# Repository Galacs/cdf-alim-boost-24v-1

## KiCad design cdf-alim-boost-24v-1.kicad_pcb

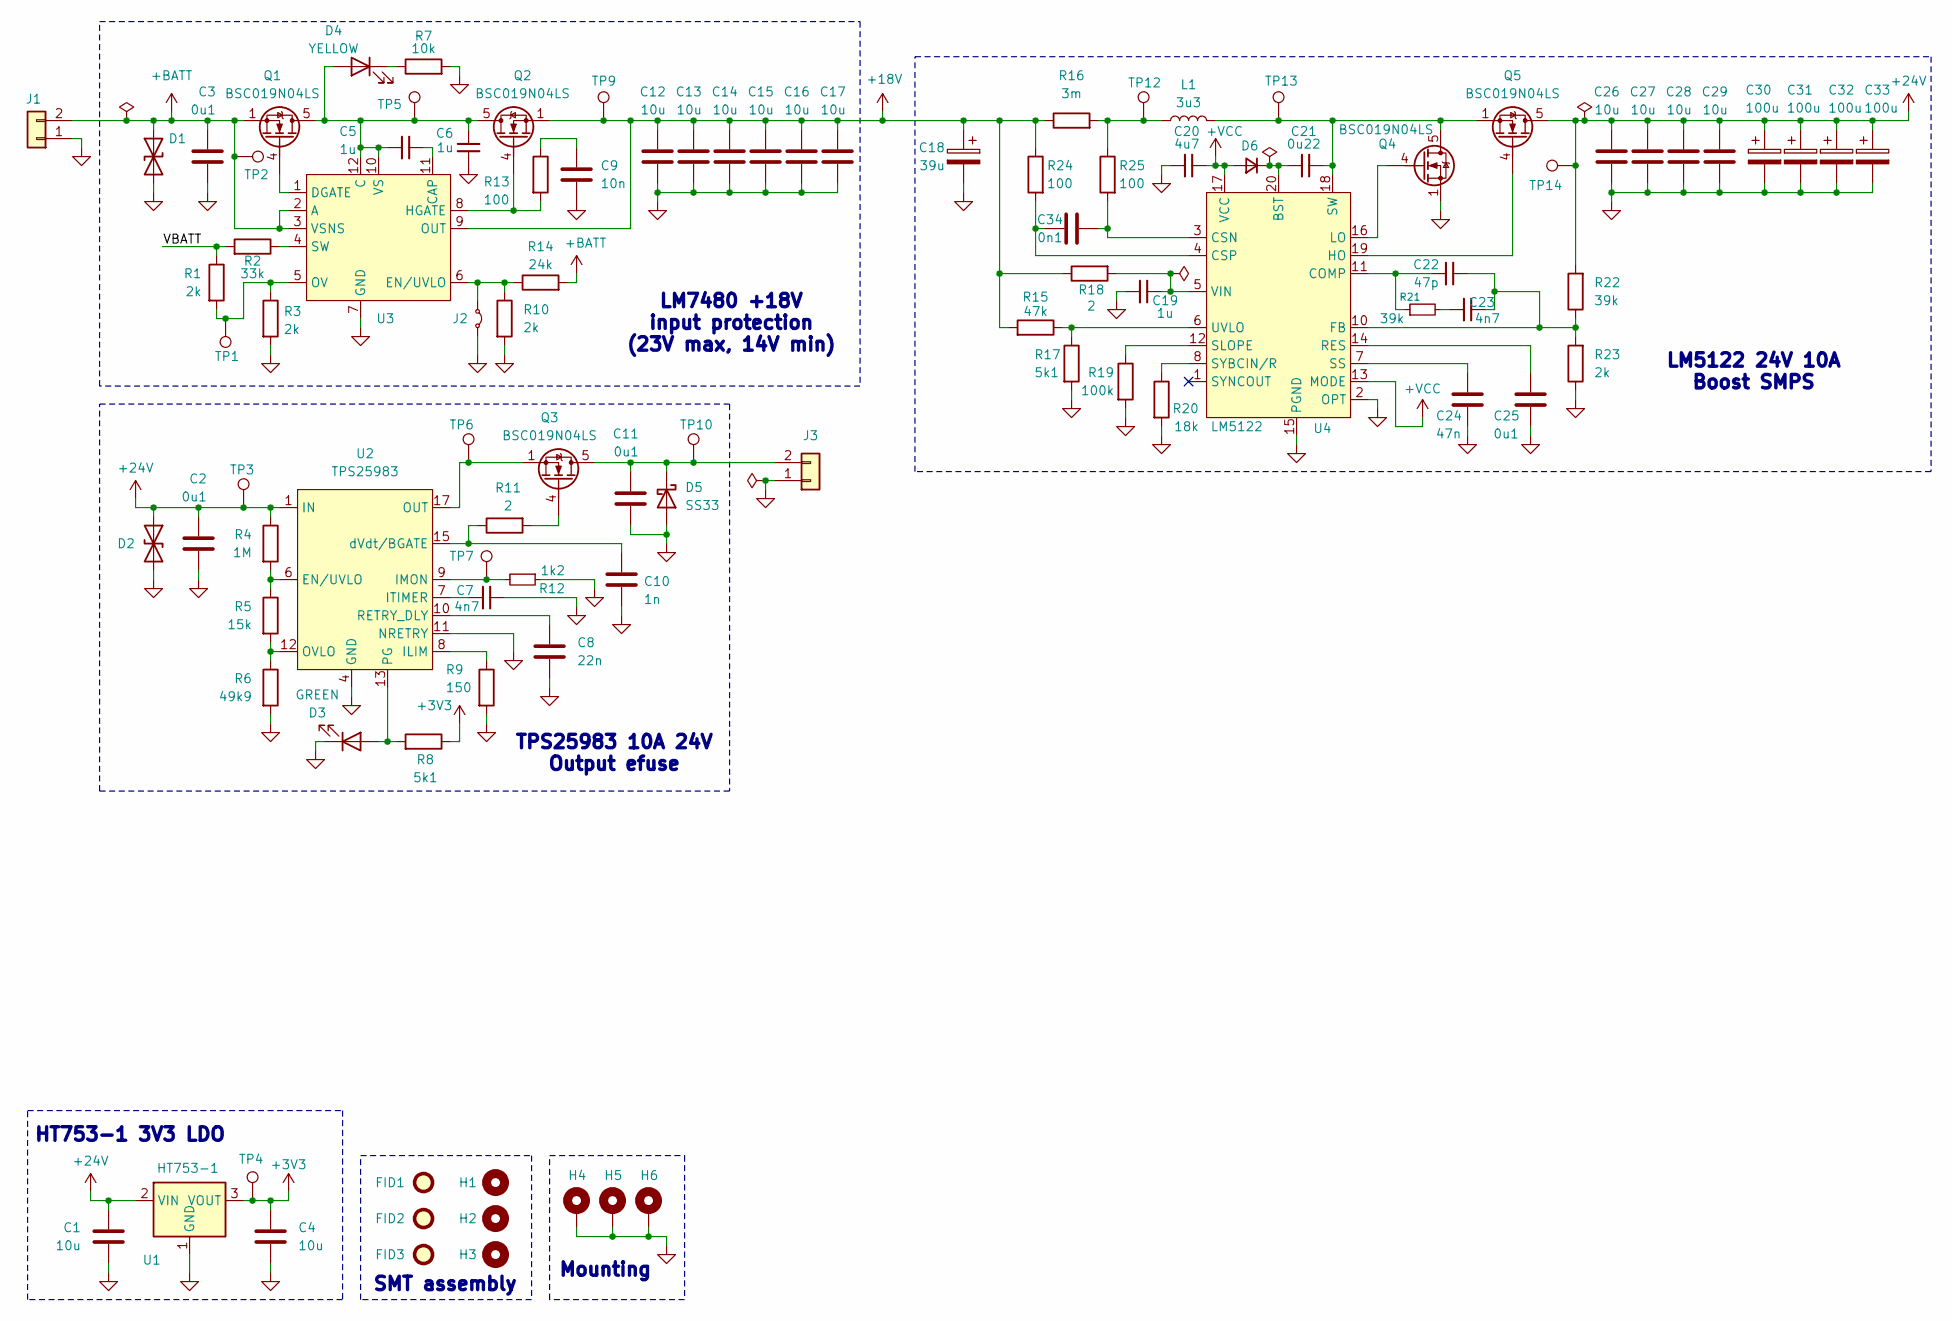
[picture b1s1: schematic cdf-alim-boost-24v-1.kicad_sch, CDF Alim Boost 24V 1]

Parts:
C1, C4: 10u; C_0805_2012Metric; Manufacturer Part Number GRM21BR61H106KE43L; JLCPCB Part # C440198
C2, C3, C11, C25: 0u1; C_0402_1005Metric; Manufacturer Part Number CL05B104KB54PNC; JLCPCB Part # C307331
C5, C6: 1u; C_0402_1005Metric; Manufacturer Part Number CL05A105KA5NQNC; JLCPCB Part # C52923
C7, C23: 4n7; C_0402_1005Metric; Manufacturer Part Number 0402B472K500NT; JLCPCB Part # C1538
C8: 22n; C_0402_1005Metric; Manufacturer Part Number 0402B223K500NT; JLCPCB Part # C1532
C9: 10n; C_0402_1005Metric; Manufacturer Part Number CL05B103KB5NNNC; JLCPCB Part # C15195
C10: 1n; C_0603_1608Metric_Pad1.08x0.95mm_HandSolder; Manufacturer Part Number CL10B102KB8NNNC; JLCPCB Part # C1588
C12, C13, C14, C15, C16, C17, C26, C27, C28, C29: 10u; C_1206_3216Metric; Manufacturer Part Number CL31A106KBHNNNE; JLCPCB Part # C13585
C18: 39u; CP_Elec_8x6.9; Manufacturer Part Number 35SVPF39M; JLCPCB Part # C189474
C19: 1u; C_0603_1608Metric_Pad1.08x0.95mm_HandSolder; Manufacturer Part Number CL10A105KB8NNNC; JLCPCB Part # C15849
C20: 4u7; C_0603_1608Metric_Pad1.08x0.95mm_HandSolder; Manufacturer Part Number CL10A475KO8NNNC; JLCPCB Part # C19666
C21: 0u22; C_0402_1005Metric; Manufacturer Part Number CL05B224KO5NNNC; JLCPCB Part # C16772
C22: 47p; C_0402_1005Metric; Manufacturer Part Number 0402CG470J500NT; JLCPCB Part # C1567
C24: 47n; R_0603_1608Metric; Manufacturer Part Number CL10B473KB8NNNC; JLCPCB Part # C1622
C30, C31, C32, C33: 100u; CP_Elec_8x10; Manufacturer Part Number RHS1V101MCN1GS; JLCPCB Part # C2162472
C34: 0n1; C_0402_1005Metric; Manufacturer Part Number 0402CG101J500NT; JLCPCB Part # C1546
D1, D2: SMAJ26CA; D_SMA; Manufacturer Part Number SMAJ26CA; JLCPCB Part # C19077544
D3: GREEN; LED_0805_2012Metric; Manufacturer Part Number KT-0805G; JLCPCB Part # C2297
D4: YELLOW; LED_0805_2012Metric; Manufacturer Part Number KT-0805Y; JLCPCB Part # C2296
D5: SS33; D_SMA; Manufacturer Part Number SS33; JLCPCB Part # C28646294
D6: D_Small; D_SMA; Manufacturer Part Number SS210; JLCPCB Part # C14996
FID1, FID2, FID3: Fiducial; Fiducial_1mm_Mask2mm
H1, H2, H3: MountingHole; ToolingHole_1.152mm
H4, H5, H6: MountingHole_Pad; MountingHole_3.2mm_M3_Pad_Via
J1: Conn_01x02; AMASS_XT30PW-M_1x02_P2.50mm_Horizontal; Manufacturer Part Number XT30PW-M30.G.Y; JLCPCB Part # C431092
J2: Conn_01x02; JST_XH_S2B-XH-A-1_1x02_P2.50mm_Horizontal; Manufacturer Part Number S2B-XH-A-1(LF)(SN); JLCPCB Part # C163035
J3: Conn_01x02; AMASS_XT30PW-F_1x02_P2.50mm_Horizontal; Manufacturer Part Number XT30PW-F20.G.Y; JLCPCB Part # C2913282
L1: 3u3; L_Sunlord_MWSA1205S-3R3; Manufacturer Part Number MWSA1205S-3R3MT; JLCPCB Part # C408513
Q1, Q2, Q3, Q4, Q5: BSC019N04LS; TDSON-8-1; Manufacturer Part Number BSC019N04LS; JLCPCB Part # C534301
R1, R3, R10, R23: 2k; R_0402_1005Metric; Manufacturer Part Number 0402WGF2001TCE; JLCPCB Part # C4109
R2: 33k; R_0402_1005Metric; Manufacturer Part Number 0402WGF3302TCE; JLCPCB Part # C25779
R4: 1M; R_0402_1005Metric; Manufacturer Part Number 0402WGF1004TCE; JLCPCB Part # C26083
R5: 15k; R_0402_1005Metric; Manufacturer Part Number 0402WGF1502TCE; JLCPCB Part # C25756
R6: 49k9; R_0603_1608Metric; Manufacturer Part Number 0603WAF4992T5E; JLCPCB Part # C23184
R7: 10k; R_0402_1005Metric; Manufacturer Part Number 0402WGF1002TCE; JLCPCB Part # C25744
R8, R17: 5k1; R_0402_1005Metric; Manufacturer Part Number 0402WGF5101TCE; JLCPCB Part # C25905
R9: 150; R_0603_1608Metric; Manufacturer Part Number 0603WAF1500T5E; JLCPCB Part # C22808
R11, R18: 2; R_0603_1608Metric; Manufacturer Part Number 0603WAF200KT5E; JLCPCB Part # C22977
R12: 1k2; R_0603_1608Metric; Manufacturer Part Number 0603WAF1201T5E; JLCPCB Part # C22765
R13, R24, R25: 100; R_0402_1005Metric; Manufacturer Part Number 0402WGF1000TCE; JLCPCB Part # C25076
R14: 24k; R_0603_1608Metric; Manufacturer Part Number 0603WAF2402T5E; JLCPCB Part # C23352
R15: 47k; R_0402_1005Metric; Manufacturer Part Number 0402WGF4702TCE; JLCPCB Part # C25792
R16: 3m; R_1020_2550Metric; Manufacturer Part Number WSL10203L000FEA; JLCPCB Part # C844481
R19: 100k; R_0402_1005Metric; Manufacturer Part Number 0402WGF1003TCE; JLCPCB Part # C25741
R20: 18k; R_0603_1608Metric; Manufacturer Part Number 0603WAF1802T5E; JLCPCB Part # C25810
R21, R22: 39k; R_0603_1608Metric; Manufacturer Part Number 0603WAF3902T5E; JLCPCB Part # C23153
TP1, TP2, TP3, TP4, TP5, TP6, TP7, TP9, TP10, TP12, TP13, TP14: TestPoint; TestPoint_Pad_D2.0mm
U1: HT753-1; SOT-89-3; Manufacturer Part Number HT7533-1; JLCPCB Part # C14289
U2: TPS25983; Texas_RGE0024M_VQFN-24-1EP_4x4mm_P0.5mm_ThermalVias; Manufacturer Part Number TPS259830ONRGER; JLCPCB Part # C20611808
U3: WSON-12-1EP_3x3mm_P0.5mm_EP1.3x2.5mm_ThermalVias; Manufacturer Part Number LM74800MDRRR; JLCPCB Part # C7216630
U4: LM5122; Texas_PWP0020A; Manufacturer Part Number LM5122MHX/NOPB; JLCPCB Part # C77241

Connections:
+3V3: C4.1, R8.1, TP4.1 (1_1), U1.3 (VOUT)
+18V: C12.1, C13.1, C14.1, C15.1, C16.1, C17.1, C18.1, Q2.1 (S), Q2.2 (S), Q2.3 (S), R15.2, R16.1, R18.1, R24.1, TP9.1 (1_1), U3.9 (OUT)
+24V: C1.1, C2.1, C26.1, C27.1, C28.1, C29.1, C30.1, C31.1, C32.1, C33.1, D2.1 (A1), Q5.5 (D), R4.1, R22.2, TP3.1 (1_1), TP14.1 (1_1), U1.2 (VIN), U2.1 (IN), U2.2 (IN), U2.3 (IN), U2.16 (IN), U2.25 (IN)
+BATT: C3.1, D1.1 (A1), J1.2, Q1.1 (S), Q1.2 (S), Q1.3 (S), R14.2, TP2.1 (1_1), U3.2 (A), U3.3 (VSNS)
+VCC: C20.1, D6.2 (A), U4.13 (MODE), U4.17 (VCC)
/VBATT: R1.1, R2.2
GND: C1.2, C2.2, C3.2, C4.2, C6.1, C7.2, C8.2, C9.2, C10.1, C11.2, C12.2, C13.2, C14.2, C15.2, C16.2, C17.2, C18.2, C19.1, C20.2, C24.2, C25.2, C26.2, C27.2, C28.2, C29.2, C30.2, C31.2, C32.2, C33.2, D1.2 (A2), D2.2 (A2), D3.1 (K), D5.2 (A), H4.1 (1_1), H5.1 (1_1), H6.1 (1_1), J1.1, J2.1 (A), J3.1, Q4.1 (S), Q4.2 (S), Q4.3 (S), R3.2, R6.2, R7.2, R9.2, R10.2, R12.1, R17.2, R19.2, R20.2, R23.1, U1.1 (GND), U2.4 (GND), U2.5 (GND), U2.11 (NRETRY), U2.14 (GND), U2.26 (GND), U3.7 (GND), U4.2 (OPT), U4.9 (AGND), U4.15 (PGND), U4.21 (EP)
unnamed: C9.1, R13.1
unnamed: C23.1, R21.2
unnamed: D3.2 (A), R8.2, U2.13 (PG)
unnamed: C5.2, C6.2, D4.2 (A), Q1.5 (D), Q2.5 (D), TP5.1 (1_1), U3.10 (VS), U3.12 (C)
unnamed: D4.1 (K), R7.1
unnamed: C11.1, D5.1 (K), J3.2, Q3.5 (D), TP10.1 (1_1)
unnamed: C21.2, D6.1 (K), U4.20 (BST)
unnamed: J2.2 (B), R10.1, R14.1, U3.6 (EN/UVLO)
unnamed: L1.1, R16.2, R25.1, TP12.1 (1_1)
unnamed: Q1.4 (G), U3.1 (DGATE)
unnamed: Q2.4 (G), R13.2, U3.8 (HGATE)
unnamed: Q3.4 (G), R11.2
unnamed: Q3.1 (S), Q3.2 (S), Q3.3 (S), TP6.1 (1_1), U2.17 (OUT), U2.18 (OUT), U2.19 (OUT), U2.20 (OUT), U2.21 (OUT), U2.22 (OUT), U2.23 (OUT), U2.24 (OUT)
unnamed: C21.1, L1.2, Q4.5 (D), Q5.1 (S), Q5.2 (S), Q5.3 (S), TP13.1 (1_1), U4.18 (SW)
unnamed: Q4.4 (G), U4.16 (LO)
unnamed: Q5.4 (G), U4.19 (HO)
unnamed: R4.2, R5.1, U2.6 (EN/UVLO)
unnamed: R9.1, U2.8 (ILIM)
unnamed: R12.2, TP7.1 (1_1), U2.9 (IMON)
unnamed: C7.1, U2.7 (ITIMER)
unnamed: R5.2, R6.1, U2.12 (OVLO)
unnamed: C8.1, U2.10 (RETRY_DLY)
unnamed: C10.2, R11.1, U2.15 (dVdt/BGATE)
unnamed: C5.1, U3.11 (CAP)
unnamed: R1.2, R3.1, TP1.1 (1_1), U3.5 (OV)
unnamed: R2.1, U3.4 (SW)
unnamed: C22.1, R21.1, U4.11 (COMP)
unnamed: C34.2, R25.2, U4.3 (CSN)
unnamed: C34.1, R24.2, U4.4 (CSP)
unnamed: C22.2, C23.2, R22.1, R23.2, U4.10 (FB)
unnamed: C25.1, U4.14 (RES)
unnamed: R19.1, U4.12 (SLOPE)
unnamed: C24.1, U4.7 (SS)
unnamed: R20.1, U4.8 (SYBCIN/R)
unnamed: R15.1, R17.1, U4.6 (UVLO)
unnamed: C19.2, R18.2, U4.5 (VIN)

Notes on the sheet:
SMT assembly
LM7480 +18V input protection (23V max, 14V min)
HT753-1 3V3 LDO
Mounting
TPS25983 10A 24V Output efuse
LM5122 24V 10A Boost SMPS

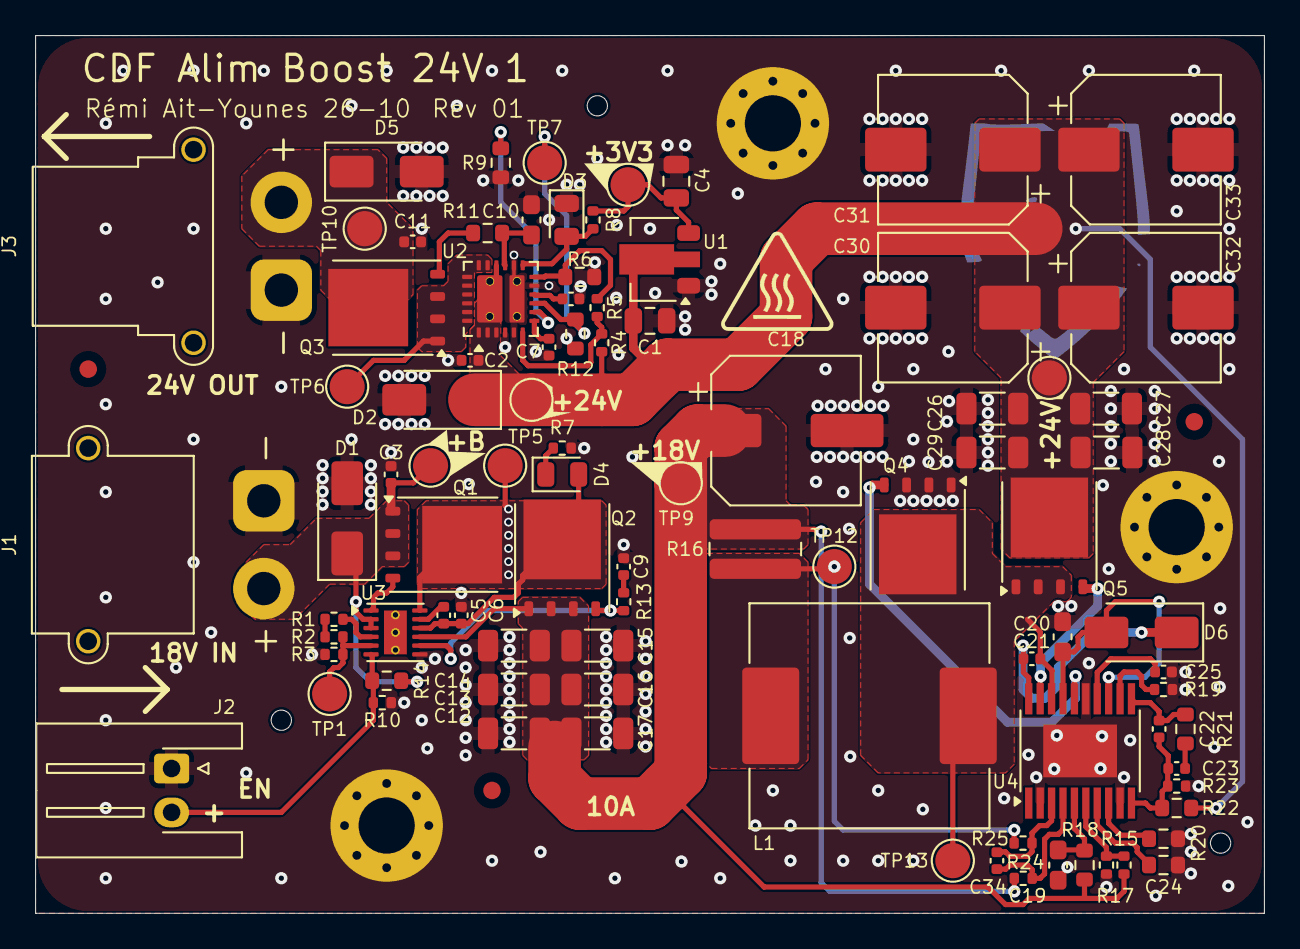
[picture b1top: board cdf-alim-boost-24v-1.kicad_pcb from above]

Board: 4 copper layers, 70.0 x 50.0 mm, 99 parts (0 on the bottom side), 43 nets.

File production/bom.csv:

Designator,Footprint,Quantity,Value,LCSC Part #
"C1, C4",0805,2,10u,C440198
C10,0603,1,1n,C1588
"C11, C2, C25, C3",0402,4,0u1,C307331
"C12, C13, C14, C15, C16, C17, C26, C27, C28, C29",1206,10,10u,C13585
C18,CP_Elec_8x6.9,1,39u,C189474
C19,0603,1,1u,C15849
C20,0603,1,4u7,C19666
C21,0402,1,0u22,C16772
C22,0402,1,47p,C1567
"C23, C7",0402,2,4n7,C1538
C24,0603,1,47n,C1622
"C30, C31, C32, C33",CP_Elec_8x10,4,100u,C2162472
C34,0402,1,0n1,C1546
"C5, C6",0402,2,1u,C52923
C8,0402,1,22n,C1532
C9,0402,1,10n,C15195
"D1, D2",D_SMA,2,SMAJ26CA,C19077544
D3,0805,1,GREEN,C2297
D4,0805,1,YELLOW,C2296
D5,D_SMA,1,SS33,C28646294
D6,D_SMA,1,D_Small,C14996
J1,AMASS_XT30PW-M_1x02_P2.50mm_Horizontal,1,Conn_01x02,C431092
J2,JST_XH_S2B-XH-A-1_1x02_P2.50mm_Horizontal,1,Conn_01x02,C163035
J3,AMASS_XT30PW-F_1x02_P2.50mm_Horizontal,1,Conn_01x02,C2913282
L1,L_Sunlord_MWSA1205S-3R3,1,3u3,C408513
"Q1, Q2, Q3, Q4, Q5",TDSON-8-1,5,BSC019N04LS,C534301
"R1, R10, R23, R3",0402,4,2k,C4109
"R11, R18",0603,2,2,C22977
R12,0603,1,1k2,C22765
"R13, R24, R25",0402,3,100,C25076
R14,0603,1,24k,C23352
R15,0402,1,47k,C25792
R16,1020,1,3m,C844481
"R17, R8",0402,2,5k1,C25905
R19,0402,1,100k,C25741
R2,0402,1,33k,C25779
R20,0603,1,18k,C25810
"R21, R22",0603,2,39k,C23153
R4,0402,1,1M,C26083
R5,0402,1,15k,C25756
R6,0603,1,49k9,C23184
R7,0402,1,10k,C25744
R9,0603,1,150,C22808
U1,SOT-89-3,1,HT753-1,C14289
U2,Texas_RGE0024M_VQFN-24-1EP_4x4mm_P0.5mm_ThermalVias,1,TPS25983,C20611808
U3,WSON-12-1EP_3x3mm_P0.5mm_EP1.3x2.5mm_ThermalVias,1,~,C7216630
U4,Texas_PWP0020A,1,LM5122,C77241
